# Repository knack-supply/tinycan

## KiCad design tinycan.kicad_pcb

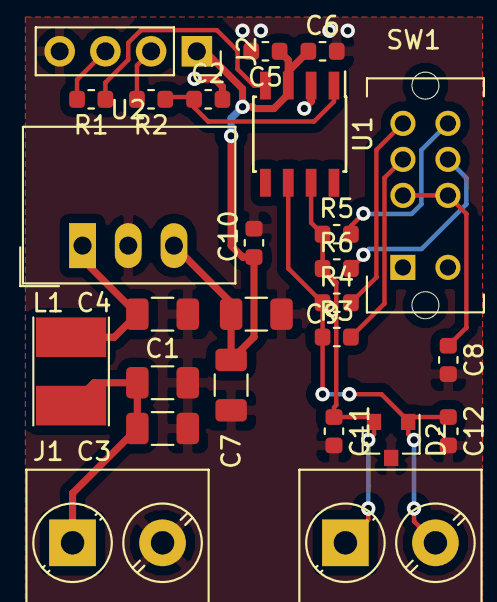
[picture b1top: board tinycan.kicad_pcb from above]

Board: 2 copper layers, 26 parts (0 on the bottom side), 15 nets.

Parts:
C1, C9: 2.2u; C_1206_3216Metric
C2, C11, C12: 47p; C_0603_1608Metric
C3, C4, C7: 10u; C_1206_3216Metric
C5, C8: 47n; C_0603_1608Metric
C6, C10: 470n; C_0603_1608Metric
D2: ESDCAN24-2BLY; SOT-23
J1, J3: Screw_Terminal_01x02; TerminalBlock_Phoenix_PT-1,5-2-5.0-H_1x02_P5.00mm_Horizontal
J2: Conn_01x04_Male; PinSocket_1x04_P2.54mm_Vertical
L1: 12u; L_Taiyo-Yuden_NR-40xx_HandSoldering
R1, R2, R4, R5: 59; R_0603_1608Metric
R3, R6: 1.5k; R_0603_1608Metric
SW1: SW_DP3T; SW_CuK_OS203011MA2QP1_DP3T_Angled
U1: TCAN332; SOIC-8_3.9x4.9mm_P1.27mm
U2: R-783.3-0.5; Converter_DCDC_RECOM_R-78E-0.5_THT

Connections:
+3V3: C5.1, C6.1, C7.1, C9.1, C10.1, J2.1, U1.3, U2.3
/CANH: C11.1, D2.2, J3.1, R5.1, R6.1, U1.7
/CANL: C12.1, D2.1, J3.2, R3.1, R4.1, U1.6
/CANRX: J2.3, R1.2
/CANTX: J2.2, R2.2
/Vin: C1.1, C3.1, J1.1, L1.1
/VinF: C4.1, L1.2, U2.1
GND: C1.2, C2.2, C3.2, C4.2, C5.2, C6.2, C7.2, C8.2, C9.2, C10.2, C11.2, C12.2, D2.3, J1.2, J2.4, U1.2, U2.2
unnamed: C2.1, R2.1, U1.1
unnamed: C8.1, SW1.2, SW1.6
unnamed: R1.1, U1.4
unnamed: R3.2, SW1.3
unnamed: R4.2, SW1.4
unnamed: R5.2, SW1.8
unnamed: R6.2, SW1.7

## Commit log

2018-07-17 initial version
